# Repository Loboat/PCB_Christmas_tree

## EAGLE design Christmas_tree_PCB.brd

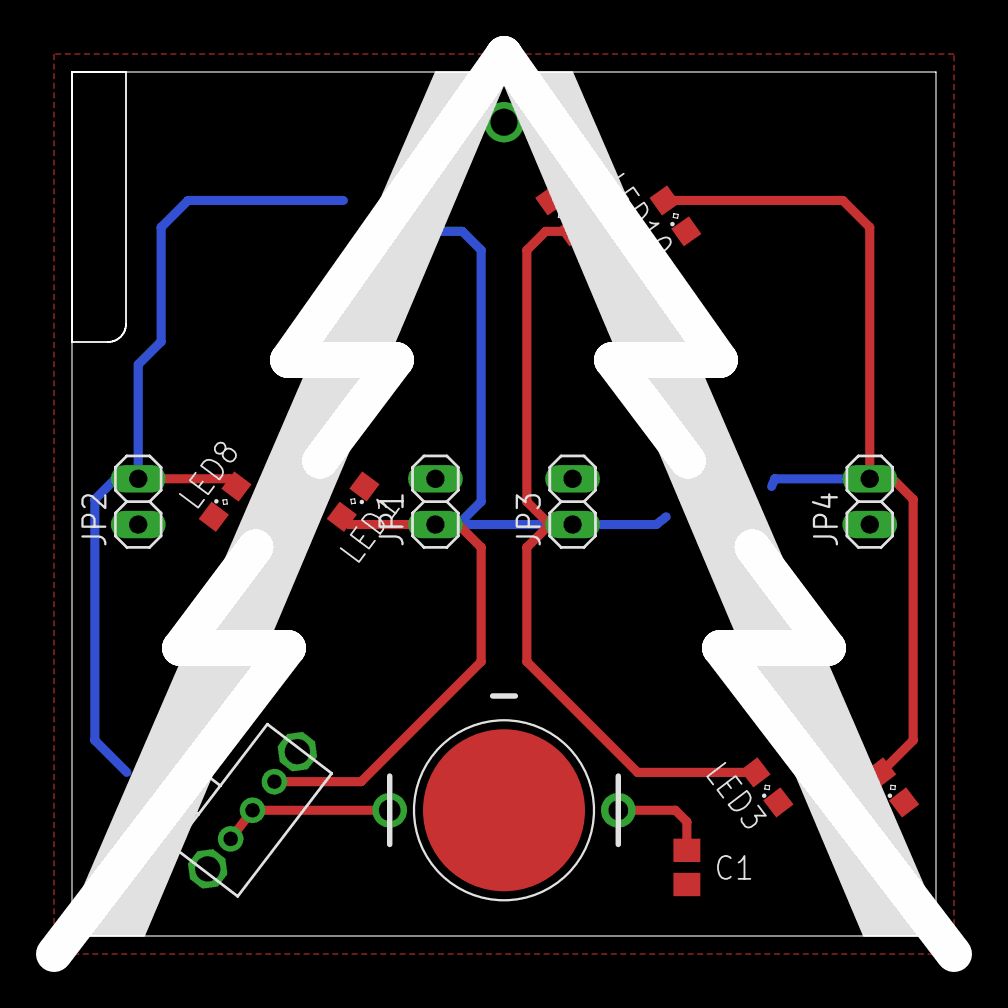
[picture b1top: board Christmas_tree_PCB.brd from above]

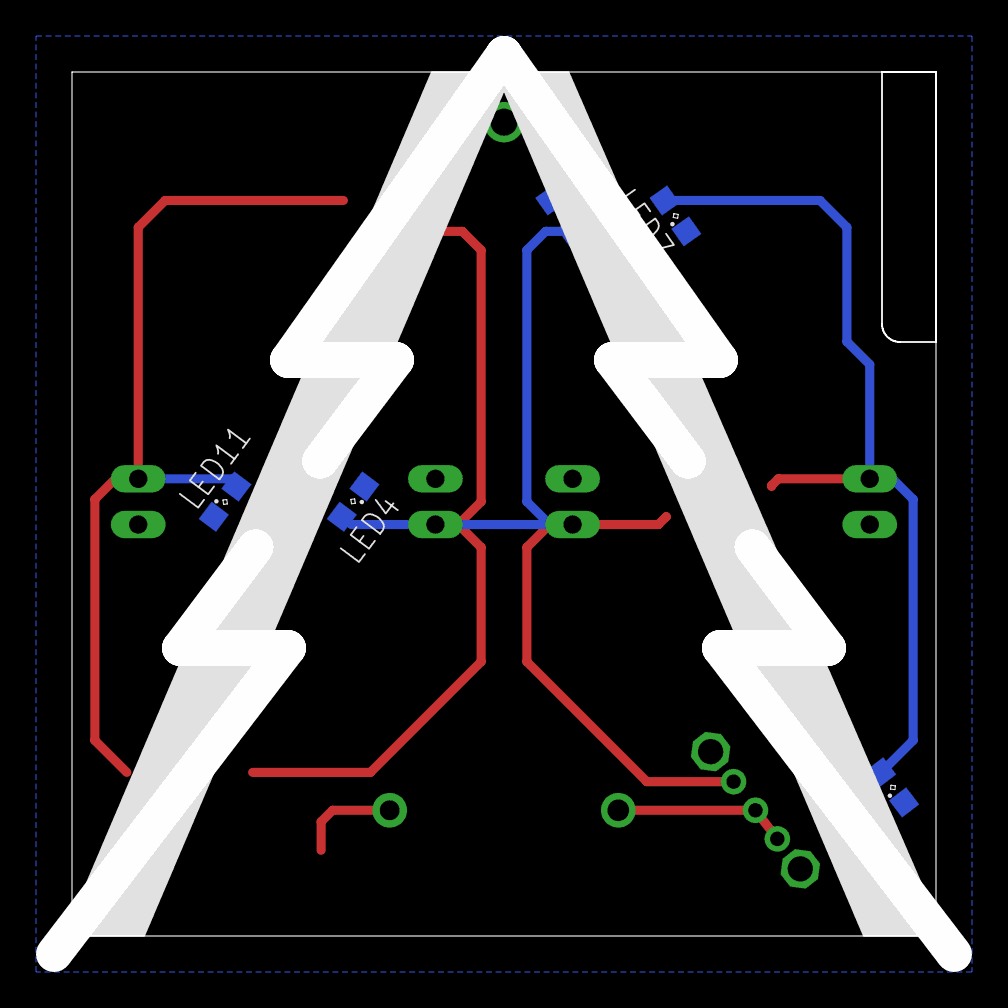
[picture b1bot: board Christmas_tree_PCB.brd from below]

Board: 2 copper layers, 50.0 x 50.0 mm, 18 parts (5 on the bottom side), 5 nets.

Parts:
C1: 10uf; C0805
JP1, JP2, JP3, JP4: 1X02
LED1, LED2, LED3, LED4, LED5, LED7, LED8, LED9, LED10, LED11, LED12: SML0805
U$1: CR1220_METAL_HOLDER
U$2: SK-12D07

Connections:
GND: C1.2, JP1.2, JP2.1, JP3.2, JP4.1, LED1.C, LED2.C, LED3.C, LED4.C, LED5.C, LED7.C, LED8.C, LED9.C, LED10.C, LED11.C, LED12.C, U$1.P$3, U$2.P$4, U$2.P$5
unnamed: C1.1, U$1.P$1, U$1.P$2, U$2.P$1, U$2.P$2
unnamed: JP2.2, LED7.A, LED8.A, LED9.A
unnamed: JP4.2, LED10.A, LED11.A, LED12.A
unnamed: JP1.1, JP3.1, LED1.A, LED2.A, LED3.A, LED4.A, LED5.A, U$2.P$3

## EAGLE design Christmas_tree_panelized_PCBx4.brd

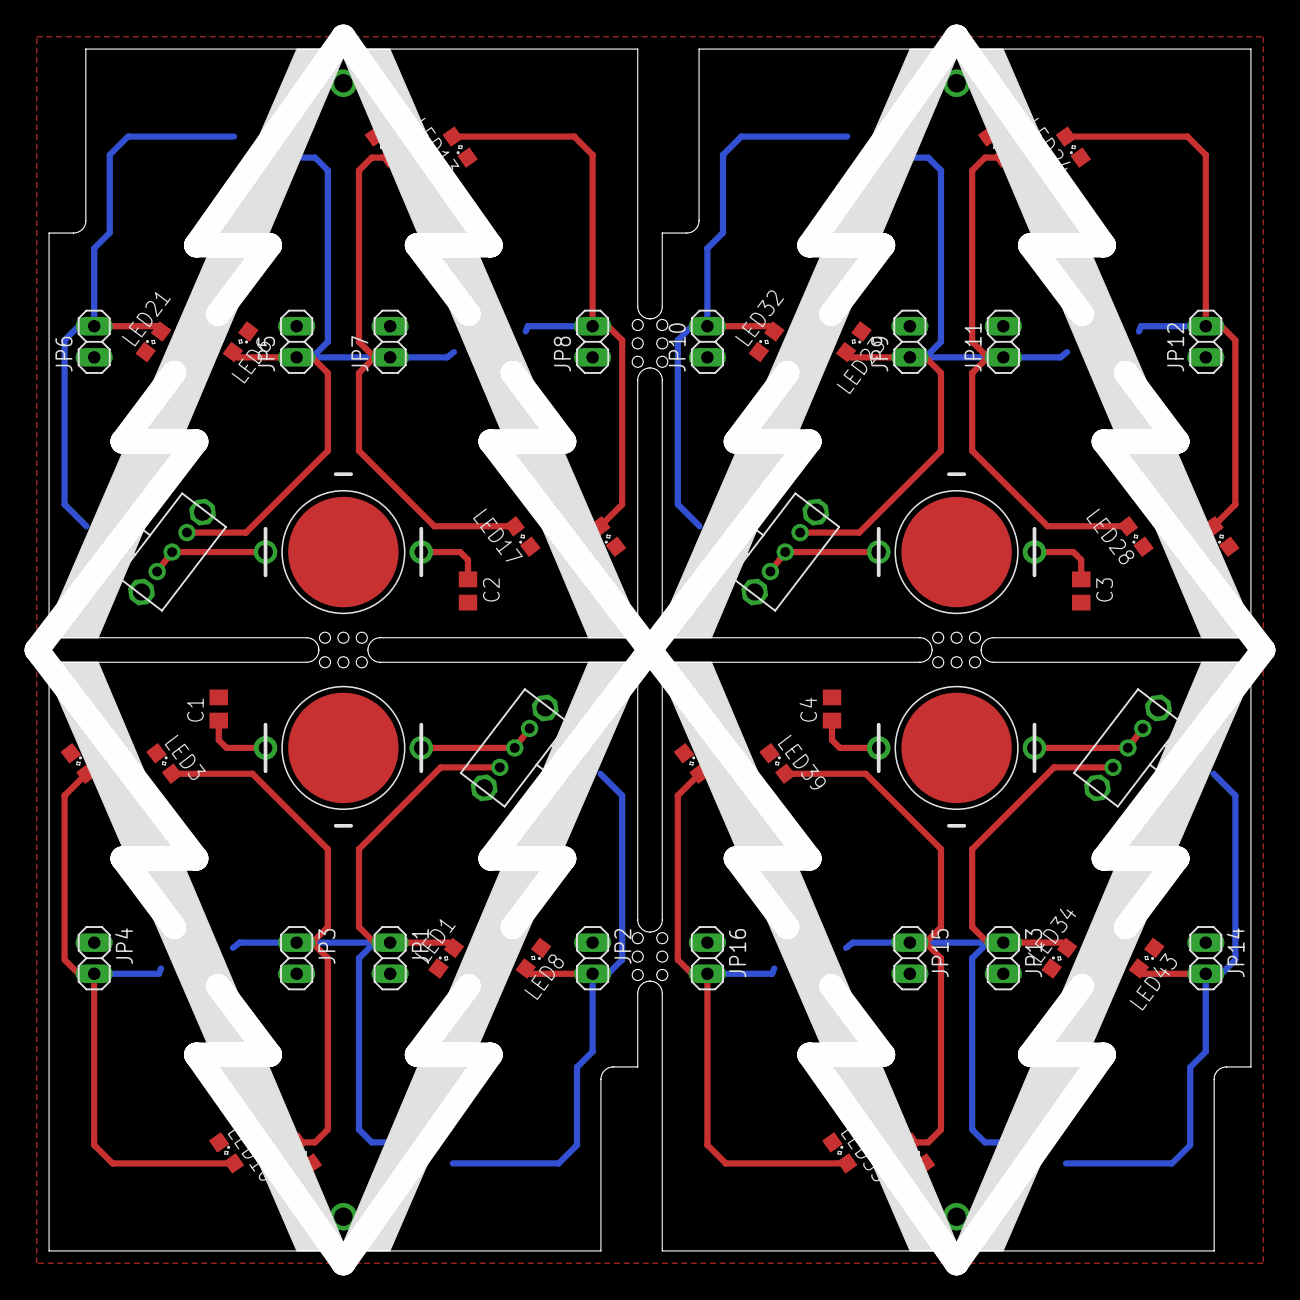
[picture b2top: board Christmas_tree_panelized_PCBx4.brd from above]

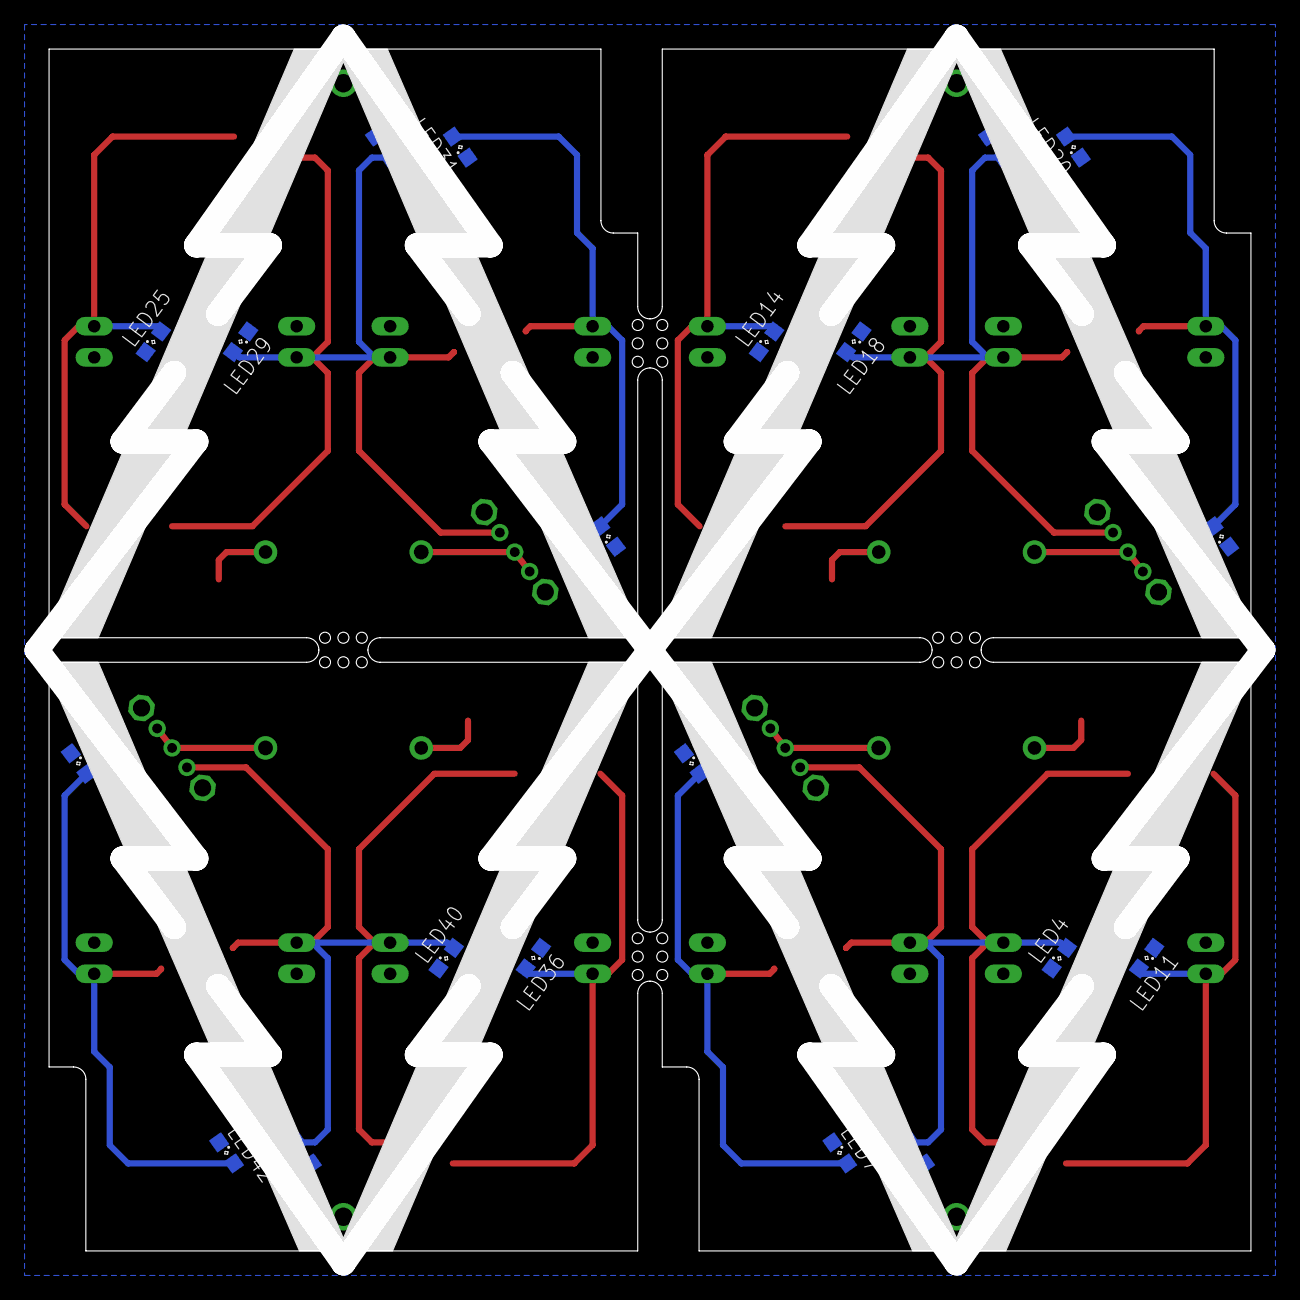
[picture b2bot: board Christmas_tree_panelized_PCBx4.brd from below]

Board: 2 copper layers, 100.0 x 100.0 mm, 72 parts (20 on the bottom side), 17 nets.

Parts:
C1, C2, C3, C4: 10uf; C0805
JP1, JP2, JP3, JP4, JP5, JP6, JP7, JP8, JP9, JP10, JP11, JP12, JP13, JP14, JP15, JP16: 1X02
LED1, LED2, LED3, LED4, LED5, LED6, LED7, LED8, LED9, LED10, LED11, LED12, LED13, LED14, LED15, LED16, LED17, LED18, LED19, LED20, LED21, LED22, LED23, LED24, LED25, LED26, LED27, LED28, LED29, LED30, LED31, LED32, LED33, LED34, LED35, LED36, LED37, LED38, LED39, LED40, LED41, LED42, LED43, LED44: SML0805
U$1, U$3, U$5, U$7: CR1220_METAL_HOLDER
U$2, U$4, U$6, U$8: SK-12D07

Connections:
GND: C1.2, C2.2, C3.2, C4.2, JP1.2, JP2.1, JP3.2, JP4.1, JP5.2, JP6.1, JP7.2, JP8.1, JP9.2, JP10.1, JP11.2, JP12.1, JP13.2, JP14.1, JP15.2, JP16.1, LED1.C, LED2.C, LED3.C, LED4.C, LED5.C, LED6.C, LED7.C, LED8.C, LED9.C, LED10.C, LED11.C, LED12.C, LED13.C, LED14.C, LED15.C, LED16.C, LED17.C, LED18.C, LED19.C, LED20.C, LED21.C, LED22.C, LED23.C, LED24.C, LED25.C, LED26.C, LED27.C, LED28.C, LED29.C, LED30.C, LED31.C, LED32.C, LED33.C, LED34.C, LED35.C, LED36.C, LED37.C, LED38.C, LED39.C, LED40.C, LED41.C, LED42.C, LED43.C, LED44.C, U$1.P$3, U$2.P$4, U$2.P$5, U$3.P$3, U$4.P$4, U$4.P$5, U$5.P$3, U$6.P$4, U$6.P$5, U$7.P$3, U$8.P$4, U$8.P$5
unnamed: C1.1, U$1.P$1, U$1.P$2, U$2.P$1, U$2.P$2
unnamed: JP2.2, LED7.A, LED8.A, LED9.A
unnamed: JP4.2, LED10.A, LED11.A, LED12.A
unnamed: JP6.2, LED20.A, LED21.A, LED22.A
unnamed: JP1.1, JP3.1, LED1.A, LED2.A, LED3.A, LED4.A, LED5.A, U$2.P$3
unnamed: JP8.2, LED13.A, LED14.A, LED15.A
unnamed: JP5.1, JP7.1, LED6.A, LED16.A, LED17.A, LED18.A, LED19.A, U$4.P$3
unnamed: C2.1, U$3.P$1, U$3.P$2, U$4.P$1, U$4.P$2
unnamed: JP10.2, LED31.A, LED32.A, LED33.A
unnamed: JP12.2, LED24.A, LED25.A, LED26.A
unnamed: JP9.1, JP11.1, LED23.A, LED27.A, LED28.A, LED29.A, LED30.A, U$6.P$3
unnamed: C3.1, U$5.P$1, U$5.P$2, U$6.P$1, U$6.P$2
unnamed: JP14.2, LED42.A, LED43.A, LED44.A
unnamed: JP16.2, LED35.A, LED36.A, LED37.A
unnamed: JP13.1, JP15.1, LED34.A, LED38.A, LED39.A, LED40.A, LED41.A, U$8.P$3
unnamed: C4.1, U$7.P$1, U$7.P$2, U$8.P$1, U$8.P$2
